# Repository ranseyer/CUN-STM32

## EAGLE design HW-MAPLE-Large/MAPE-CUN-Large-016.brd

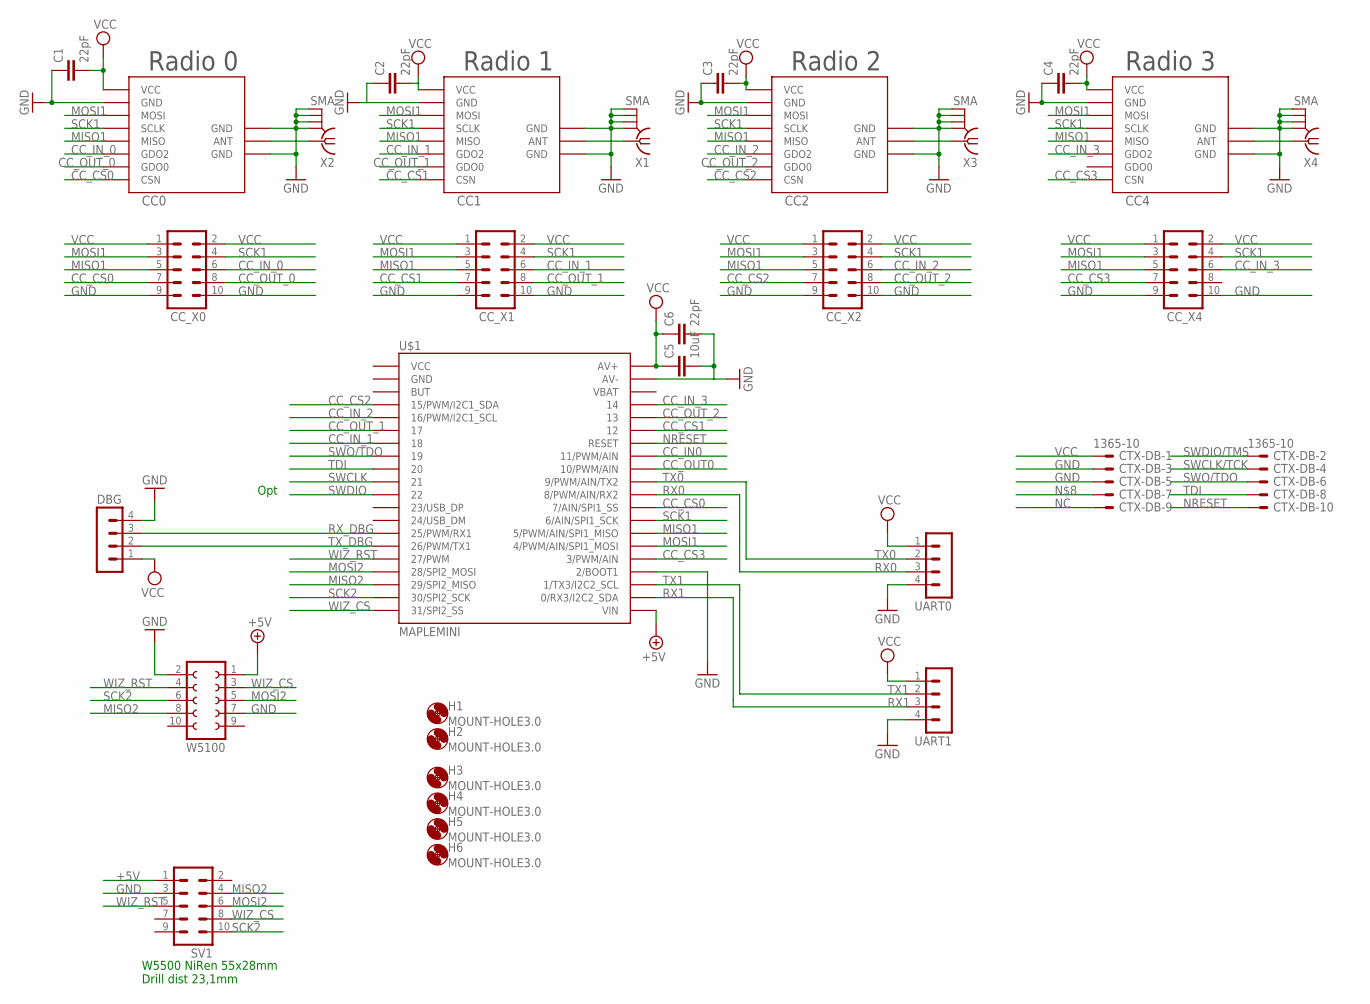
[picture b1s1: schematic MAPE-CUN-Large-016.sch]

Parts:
C1, C2, C3, C4, C6: 22pF; C0805
C5: 10uF; C1210
CC0, CC1, CC2, CC4: CC1101_MODULE1SMD; CC1101_MODULE1_SMD
CC_X0, CC_X1, CC_X2, CC_X4: MA05-2
CTX-DB: 1365-10
DBG: MA04-1
H1, H2, H3, H4, H5, H6: MOUNT-HOLE3.0; 3,0
SV1: MA05-2
U$1: MAPLEMINI; 20-DIP
UART0, UART1: MA04-1
W5100: FE05-2
X1, X2, X3, X4: SMA

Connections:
+5V: SV1.1, U$1.21 (VIN), W5100.1
CC_CS0: CC0.CSN, CC_X0.7, U$1.29 (7/AIN/SPI1_SS)
CC_CS1: CC1.CSN, CC_X1.7, U$1.35 (12)
CC_CS2: CC2.CSN, CC_X2.7, U$1.4 (15/PWM/I2C1_SDA)
CC_CS3: CC4.CSN, CC_X4.7, U$1.25 (3/PWM/AIN)
CC_IN0: U$1.33 (11/PWM/AIN)
CC_IN_0: CC0.GDO2, CC_X0.6
CC_IN_1: CC1.GDO2, CC_X1.6, U$1.7 (18)
CC_IN_2: CC2.GDO2, CC_X2.6, U$1.5 (16/PWM/I2C1_SCL)
CC_IN_3: CC4.GDO2, CC_X4.6, U$1.37 (14)
CC_OUT0: U$1.32 (10/PWM/AIN)
CC_OUT_0: CC0.GDO0, CC_X0.8
CC_OUT_1: CC1.GDO0, CC_X1.8, U$1.6 (17)
CC_OUT_2: CC2.GDO0, CC_X2.8, U$1.36 (13)
GND: C1.1, C2.1, C3.1, C4.1, C5.2, C6.2, CC0.GND@0 (GND), CC0.GND@1 (GND), CC0.GND@2 (GND), CC1.GND@0 (GND), CC1.GND@1 (GND), CC1.GND@2 (GND), CC2.GND@0 (GND), CC2.GND@1 (GND), CC2.GND@2 (GND), CC4.GND@0 (GND), CC4.GND@1 (GND), CC4.GND@2 (GND), CC_X0.9, CC_X0.10, CC_X1.9, CC_X1.10, CC_X2.9, CC_X2.10, CC_X4.9, CC_X4.10, CTX-DB.3, CTX-DB.5, DBG.4, SV1.3, U$1.24 (2/BOOT1), U$1.39 (AV-), UART0.4, UART1.4, W5100.2, W5100.7, X1.GND@1 (2), X1.GND@2 (3), X1.GND@3 (4), X1.GND@4 (5), X2.GND@1 (2), X2.GND@2 (3), X2.GND@3 (4), X2.GND@4 (5), X3.GND@1 (2), X3.GND@2 (3), X3.GND@3 (4), X3.GND@4 (5), X4.GND@1 (2), X4.GND@2 (3), X4.GND@3 (4), X4.GND@4 (5)
MISO1: CC0.MISO, CC1.MISO, CC2.MISO, CC4.MISO, CC_X0.5, CC_X1.5, CC_X2.5, CC_X4.5, U$1.27 (5/PWM/AIN/SPI1_MISO)
MISO2: SV1.4, U$1.18 (29/SPI2_MISO), W5100.8
MOSI1: CC0.MOSI, CC1.MOSI, CC2.MOSI, CC4.MOSI, CC_X0.3, CC_X1.3, CC_X2.3, CC_X4.3, U$1.26 (4/PWM/AIN/SPI1_MOSI)
MOSI2: SV1.6, U$1.17 (28/SPI2_MOSI), W5100.5
unnamed: CC2.ANT, X3.1
unnamed: CC4.ANT, X4.1
unnamed: CC1.ANT, X1.1
unnamed: CC0.ANT, X2.1
NC: CTX-DB.9
NRESET: CTX-DB.10, U$1.34 (RESET)
RX0: U$1.30 (8/PWM/AIN/RX2), UART0.3
RX1: U$1.22 (0/RX3/I2C2_SDA), UART1.3
RX_DBG: DBG.3, U$1.14 (25/PWM/RX1)
SCK1: CC0.SCLK, CC1.SCLK, CC2.SCLK, CC4.SCLK, CC_X0.4, CC_X1.4, CC_X2.4, CC_X4.4, U$1.28 (6/AIN/SPI1_SCK)
SCK2: SV1.10, U$1.19 (30/SPI2_SCK), W5100.6
SWCLK: U$1.10 (21)
SWCLK/TCK: CTX-DB.4
SWDIO: U$1.11 (22)
SWDIO/TMS: CTX-DB.2
SWO/TDO: CTX-DB.6, U$1.8 (19)
TDI: CTX-DB.8, U$1.9 (20)
TX0: U$1.31 (9/PWM/AIN/TX2), UART0.2
TX1: U$1.23 (1/TX3/I2C2_SCL), UART1.2
TX_DBG: DBG.2, U$1.15 (26/PWM/TX1)
VCC: C1.2, C2.2, C3.2, C4.2, C5.1, C6.1, CC0.VCC, CC1.VCC, CC2.VCC, CC4.VCC, CC_X0.1, CC_X0.2, CC_X1.1, CC_X1.2, CC_X2.1, CC_X2.2, CC_X4.1, CC_X4.2, CTX-DB.1, DBG.1, U$1.40 (AV+), UART0.1, UART1.1
WIZ_CS: SV1.8, U$1.20 (31/SPI2_SS), W5100.3
WIZ_RST: SV1.5, U$1.16 (27/PWM), W5100.4

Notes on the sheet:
Radio 1
Radio 0
Opt
Radio 2
Radio 3
W5500 NiRen 55x28mm Drill dist 23,1mm

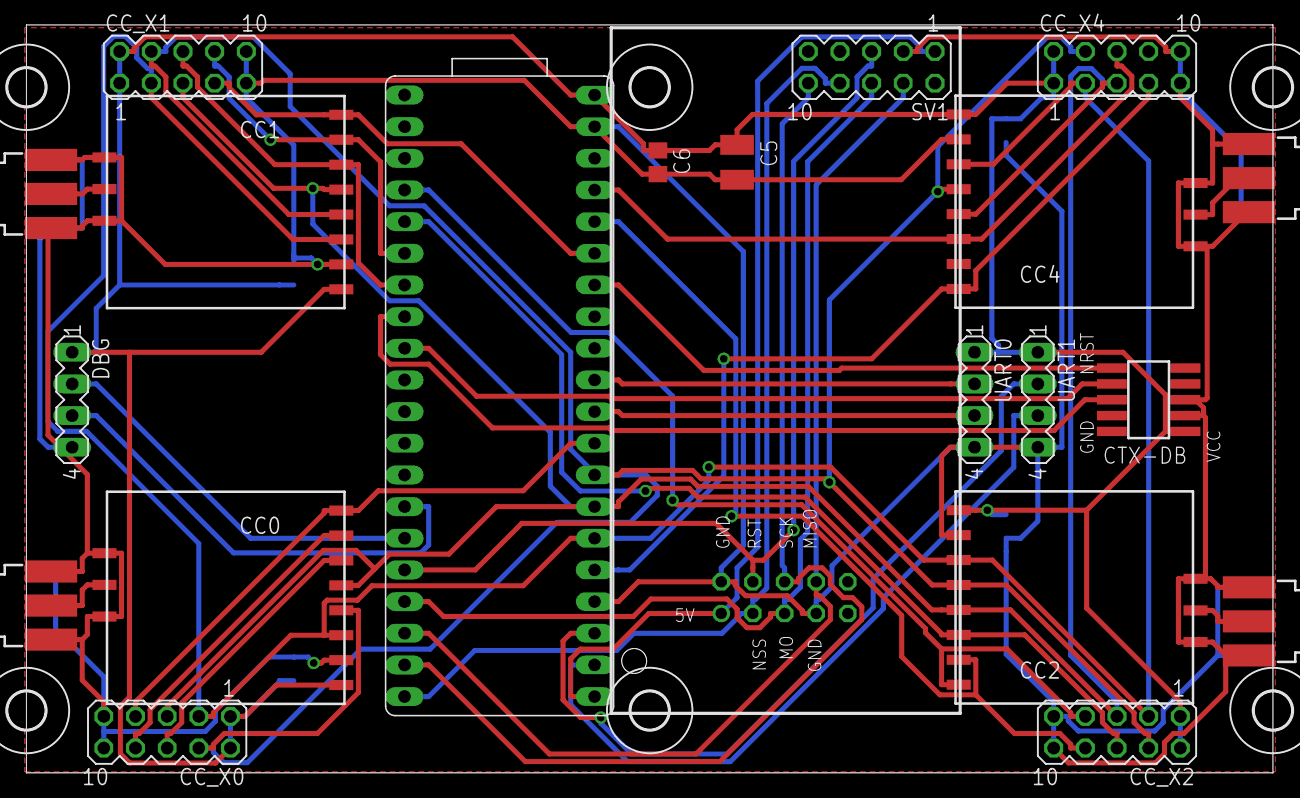
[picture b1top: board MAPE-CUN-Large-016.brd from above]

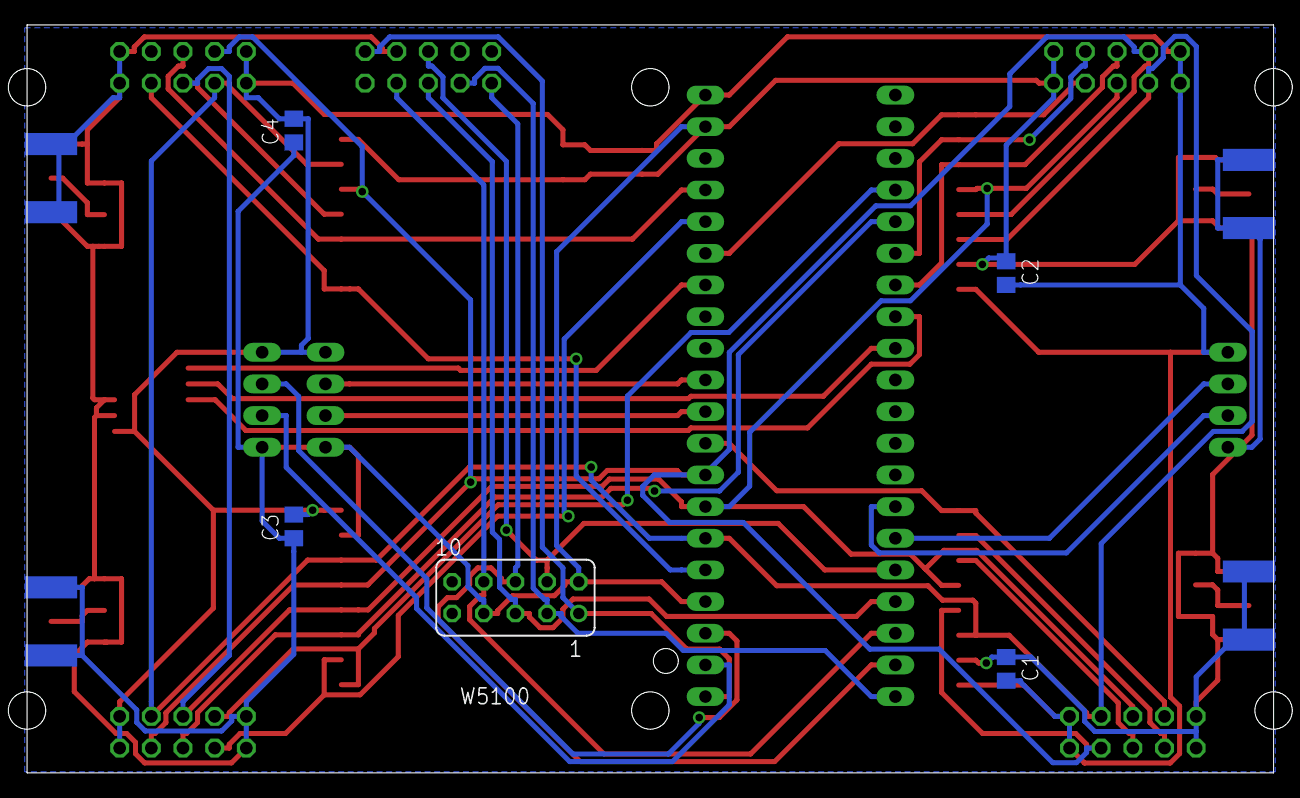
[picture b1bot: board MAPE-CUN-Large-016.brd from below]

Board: 2 copper layers, 100.0 x 60.0 mm, 31 parts (5 on the bottom side), 35 nets.

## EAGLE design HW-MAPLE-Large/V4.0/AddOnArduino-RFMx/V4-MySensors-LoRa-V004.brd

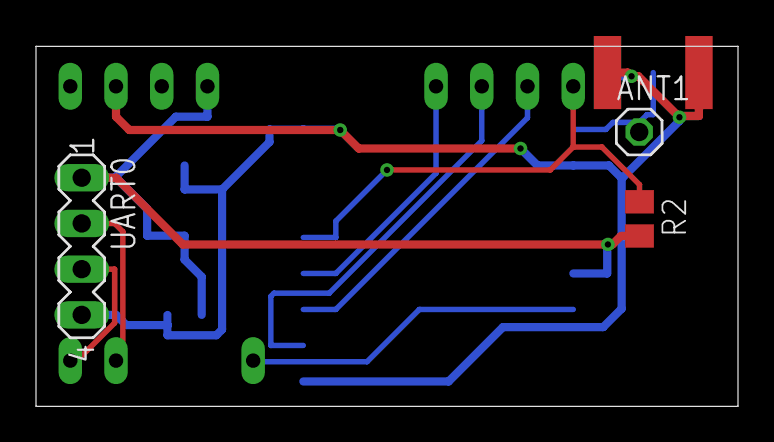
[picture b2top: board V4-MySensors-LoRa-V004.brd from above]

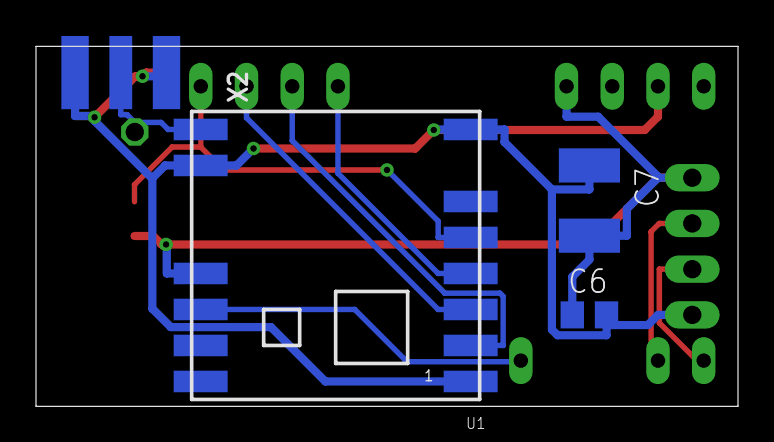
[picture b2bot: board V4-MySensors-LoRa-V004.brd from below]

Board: 2 copper layers, 39.0 x 20.0 mm, 8 parts (4 on the bottom side), 10 nets.

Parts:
ANT1: 1X01
C6: 22pF; C0805
C7: C1812
R2: 10k; M0805
U1: RFM69HCW; RFM69HCW-XXXS2
U$1: MARTIN-PROMINI-SPI; MARTIN-PRO-SPI
UART0: MA04-1
X2: SMA_EDGELAUNCH

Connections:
ANT1: ANT1.1, U1.ANT, X2.P
CSN-A: R2.1, U1.NSS, U$1.D10
GND: C6.2, C7.1, U1.GND_1, U1.GND_2, U1.GND_3, U$1.GND, UART0.4, X2.GND@1, X2.GND@2, X2.GND@3, X2.GND@4
IRQ-A: U1.DIO0, U$1.D2
MISO-A: U1.MISO, U$1.D12
MOSI-A: U1.MOSI, U$1.D11
unnamed: U$1.RX1, UART0.2
RX-MAPLE0: U$1.TX0, UART0.3
SCK-A: U1.SCK, U$1.D13
VCC: C6.1, C7.2, R2.2, U1.3.3V, U$1.VCC, UART0.1
